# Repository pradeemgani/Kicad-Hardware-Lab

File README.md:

# 🔧 KiCad Hardware Lab

A collection of practical electronics and PCB design projects developed using **KiCad**.

This repository documents my hands-on work in **analog electronics, digital electronics, power electronics, PCB design, and embedded hardware**.

---

## 📚 Projects

| # | Project | Category |
|---|---|---|
| 1 | BJT AMPLIFIER | Analog  Electronics |
| 2 | Full Wave Rectifier | Power Electronics |
| 3 | Half Wave Rectifier | Power Electronics |
| 4 | Inverting Amplifier | Analog Electronics |
| 5 | JK FLIP FLOP | Digital Electronics |
| 6 | RC PHASE SHIFT OSCILLATOR | Analog Electronics |
| 7 | SIMPLE CONTINUITY TESTER | Analog/Discrete Electronics |
| 8 | Regulator POWER SUPPLY | Power Electronics |

More projects will be added as the hardware design work continues.

---

## 🛠️ Tools & Technologies

- **KiCad** – Schematic capture and PCB design
- **PCB Layout & Design**
- **Electronic Circuit Design**
- **Analog Electronics**
- **Digital Electronics**
- **Power Electronics**
- **Gerber Generation**
- **PCB Fabrication Preparation**

---

## 📂 Repository Structure

Each project contains the KiCad design files required to open and continue working on the project.

```text
KiCad-Hardware-Lab/
│
├── /BJT AMPLIFIER
├── Full-Wave-Rectifier/
├── Half-Wave-Rectifier/
├── Inverting-Amplifier/
├── JK FLIP FLOP/
├── RC PHASE SHIFT OSCILLATOR/
├── SIMPLE CONTINUITY TESTER/
├── Regulator POWER SUPPLY/
│
└── README.md

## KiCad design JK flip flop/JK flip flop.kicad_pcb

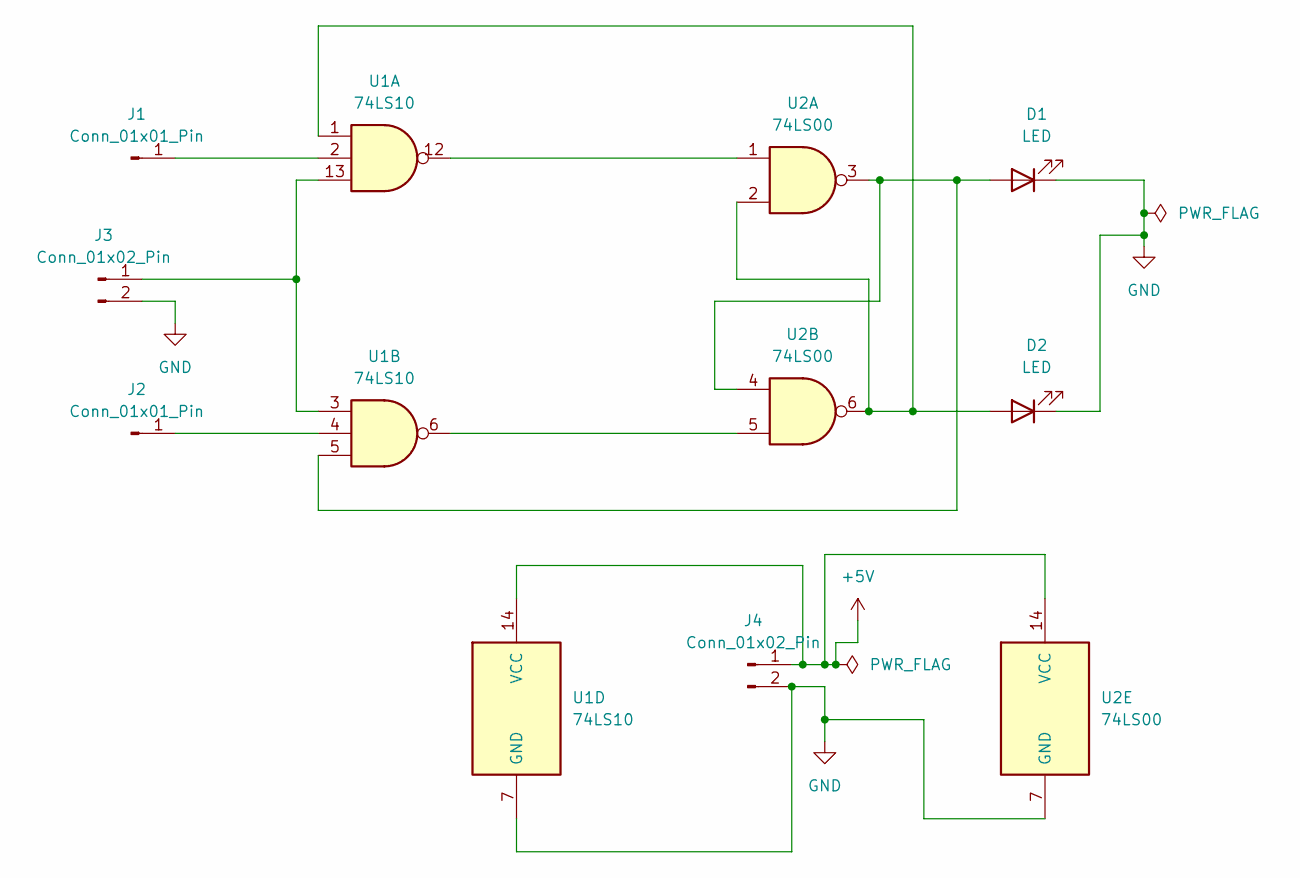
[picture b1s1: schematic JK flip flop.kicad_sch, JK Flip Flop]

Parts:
D1, D2: LED; LED_D5.0mm
J1, J2: Conn_01x01_Pin; PinHeader_1x01_P2.54mm_Vertical
J3, J4: Conn_01x02_Pin; PinHeader_1x02_P2.54mm_Vertical
U1: 74LS10; DIP-14_W7.62mm
U2: 74LS00; DIP-14_W7.62mm

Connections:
+5V: J4.1, U1.14 (VCC), U2.14 (VCC)
GND: D1.1 (K), D2.1 (K), J3.2, J4.2, U1.7 (GND), U2.7 (GND)
unnamed: D1.2 (A), U1.5, U2.3, U2.4
unnamed: D2.2 (A), U1.1, U2.2, U2.6
unnamed: J1.1 (Pin_1_1), U1.2
unnamed: J2.1 (Pin_1_1), U1.4
unnamed: J3.1, U1.3, U1.13
unnamed: U1.6, U2.5
unnamed: U1.12, U2.1

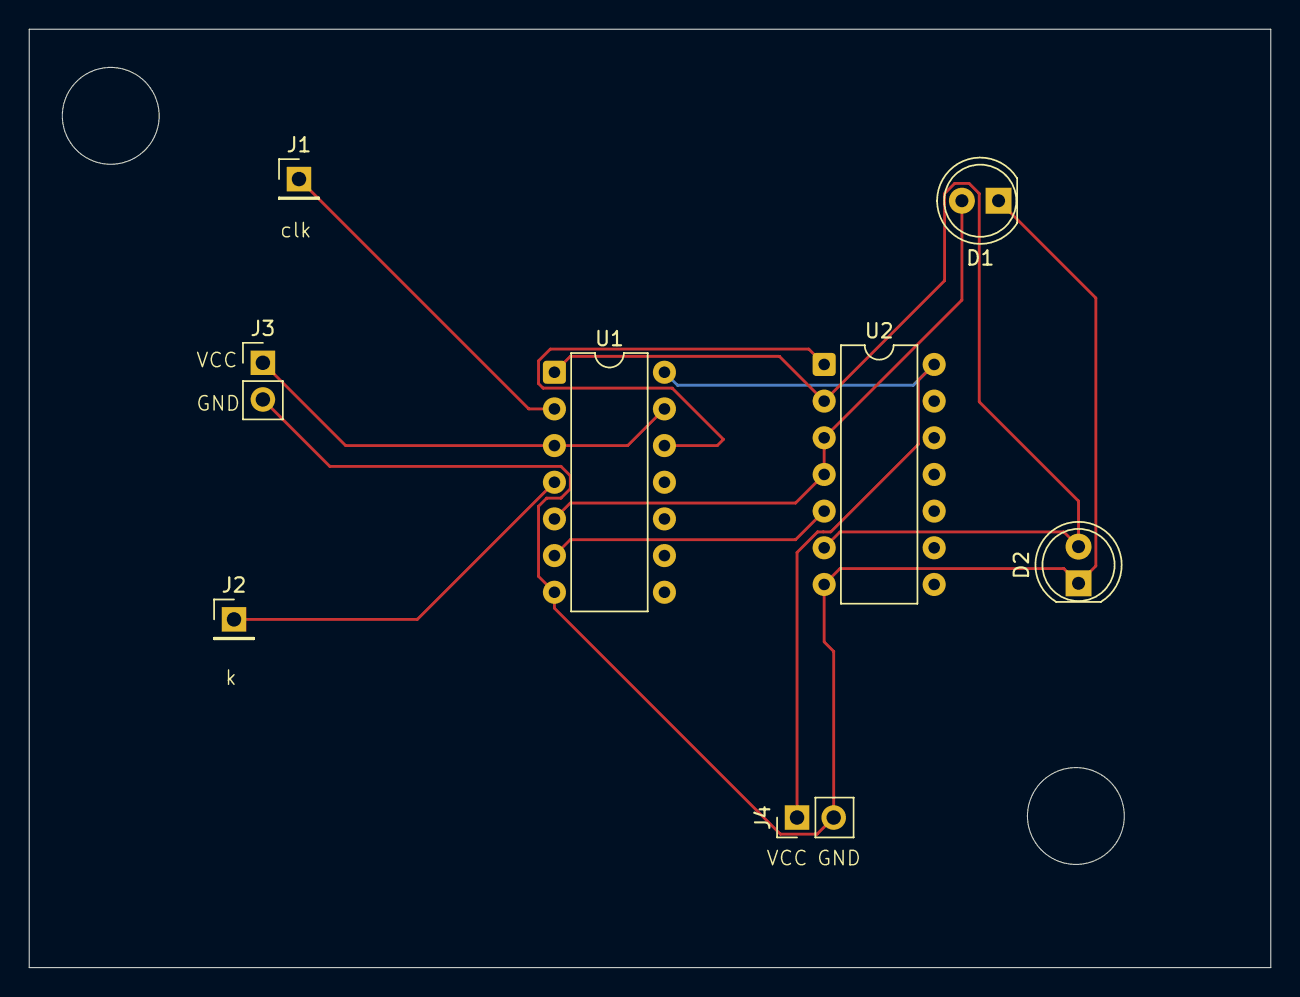
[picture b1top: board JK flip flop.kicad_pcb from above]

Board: 2 copper layers, 86.0 x 65.0 mm, 8 parts (0 on the bottom side), 9 nets.

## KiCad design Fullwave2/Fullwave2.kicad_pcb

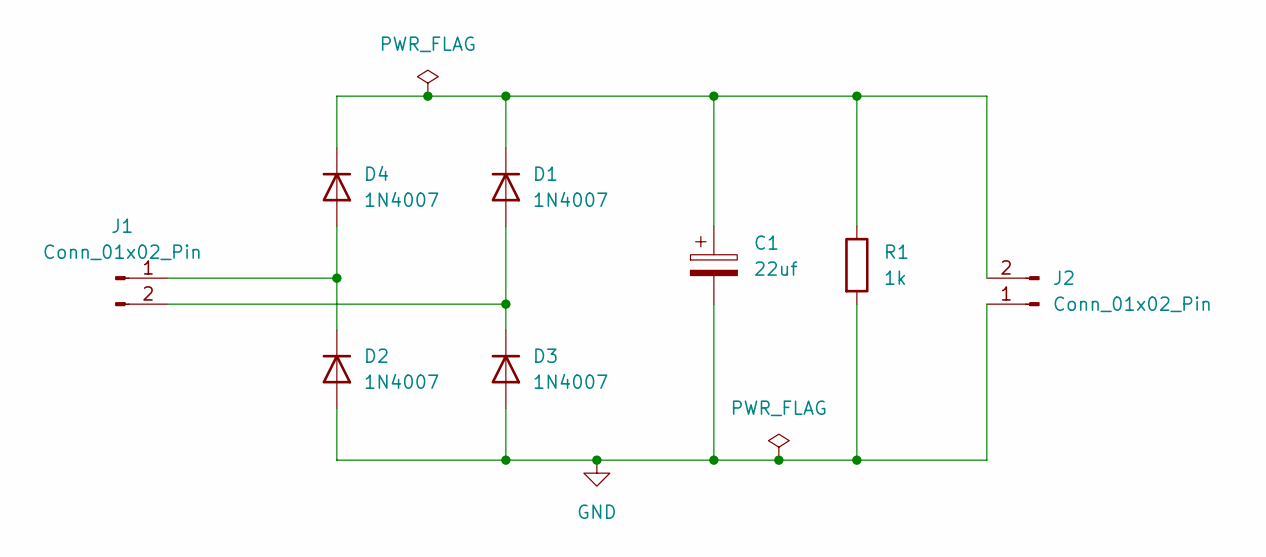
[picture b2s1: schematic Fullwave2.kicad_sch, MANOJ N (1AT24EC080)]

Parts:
C1: 22uf; CP_Radial_D6.3mm_P2.50mm
D1, D2, D3, D4: 1N4007; D_DO-41_SOD81_P10.16mm_Horizontal
J1, J2: Conn_01x02_Pin; PinHeader_1x02_P2.54mm_Vertical
R1: 1k; R_Axial_DIN0207_L6.3mm_D2.5mm_P10.16mm_Horizontal

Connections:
GND: C1.2, D2.2 (A), D3.2 (A), J2.1, R1.2
unnamed: D1.2 (A), D3.1 (K), J1.2
unnamed: C1.1, D1.1 (K), D4.1 (K), J2.2, R1.1
unnamed: D2.1 (K), D4.2 (A), J1.1

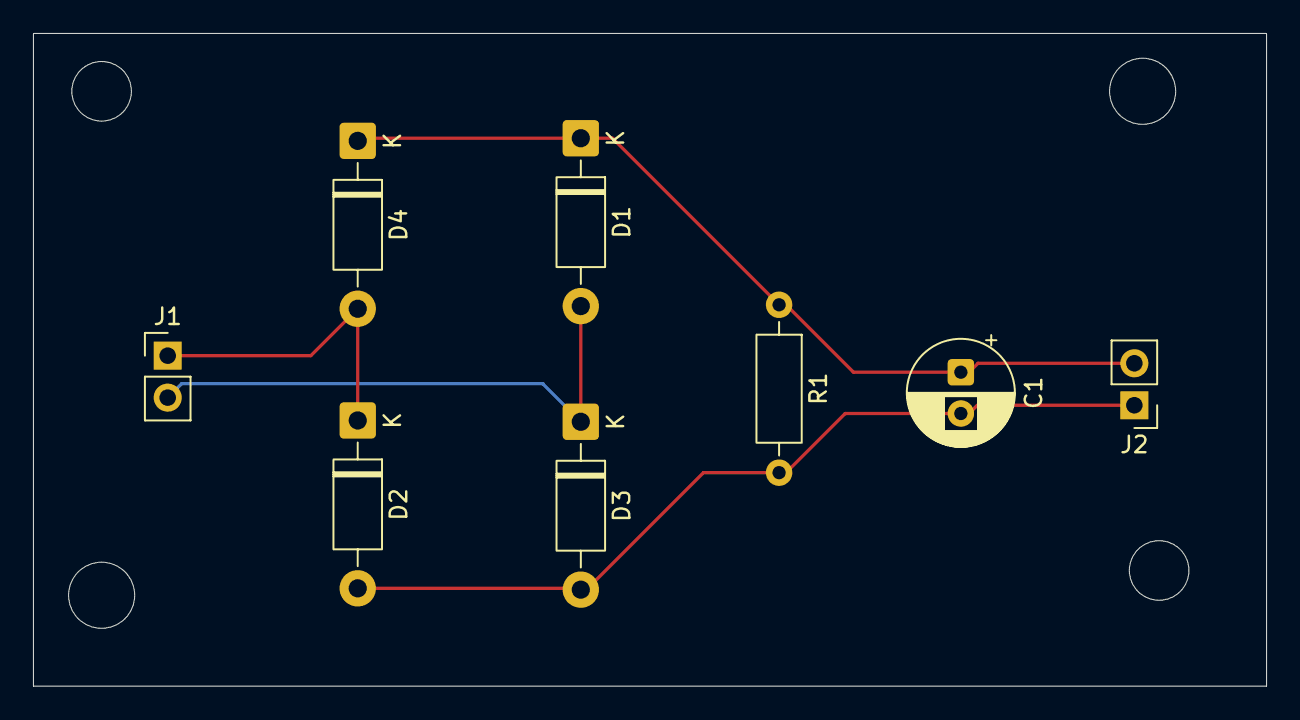
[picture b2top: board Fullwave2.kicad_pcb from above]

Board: 2 copper layers, 74.6 x 39.5 mm, 8 parts (0 on the bottom side), 4 nets.

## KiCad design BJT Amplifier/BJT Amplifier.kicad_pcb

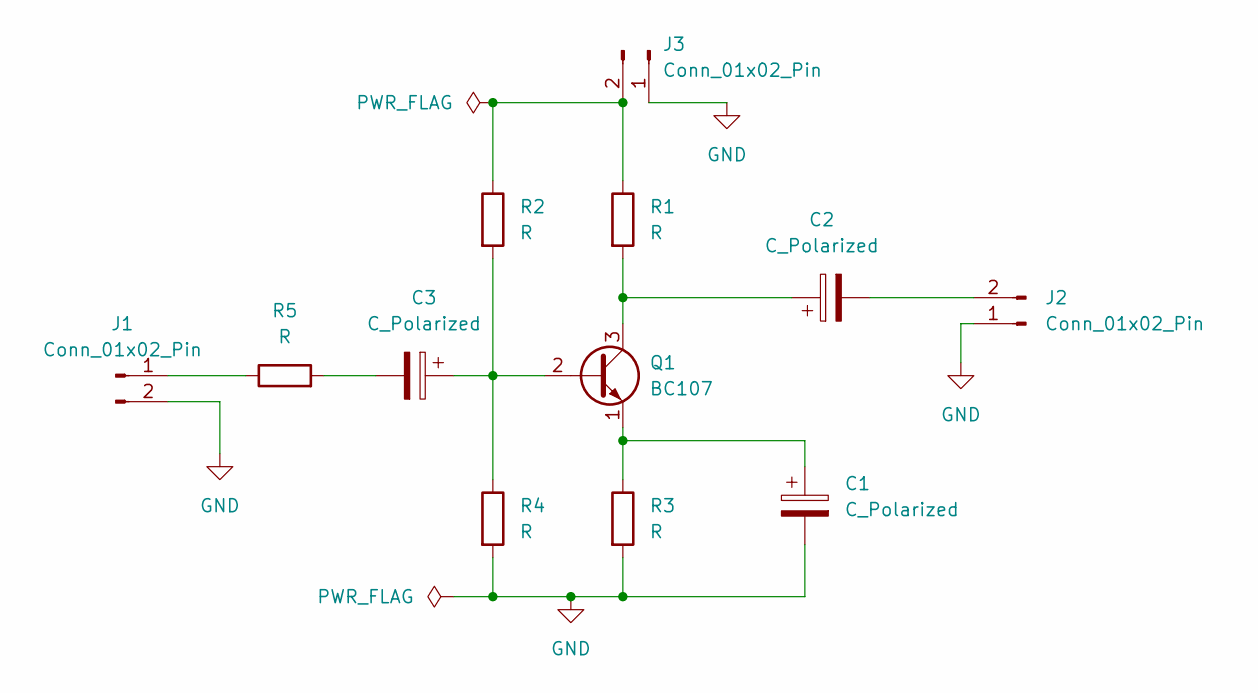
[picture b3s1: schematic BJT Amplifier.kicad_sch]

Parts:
C1, C2, C3: C_Polarized; CP_Radial_D5.0mm_P2.50mm
J1, J2, J3: Conn_01x02_Pin; PinHeader_1x02_P2.54mm_Vertical
Q1: BC107; TO-18-3
R1, R2, R3, R4, R5: R; R_Axial_DIN0207_L6.3mm_D2.5mm_P10.16mm_Horizontal

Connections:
GND: C1.2, J1.2, J2.1, J3.1, R3.2, R4.2
unnamed: C3.2, R5.2
unnamed: J1.1, R5.1
unnamed: C2.2, J2.2
unnamed: J3.2, R1.1, R2.1
unnamed: C3.1, Q1.2 (B), R2.2, R4.1
unnamed: C2.1, Q1.3 (C), R1.2
unnamed: C1.1, Q1.1 (E), R3.1

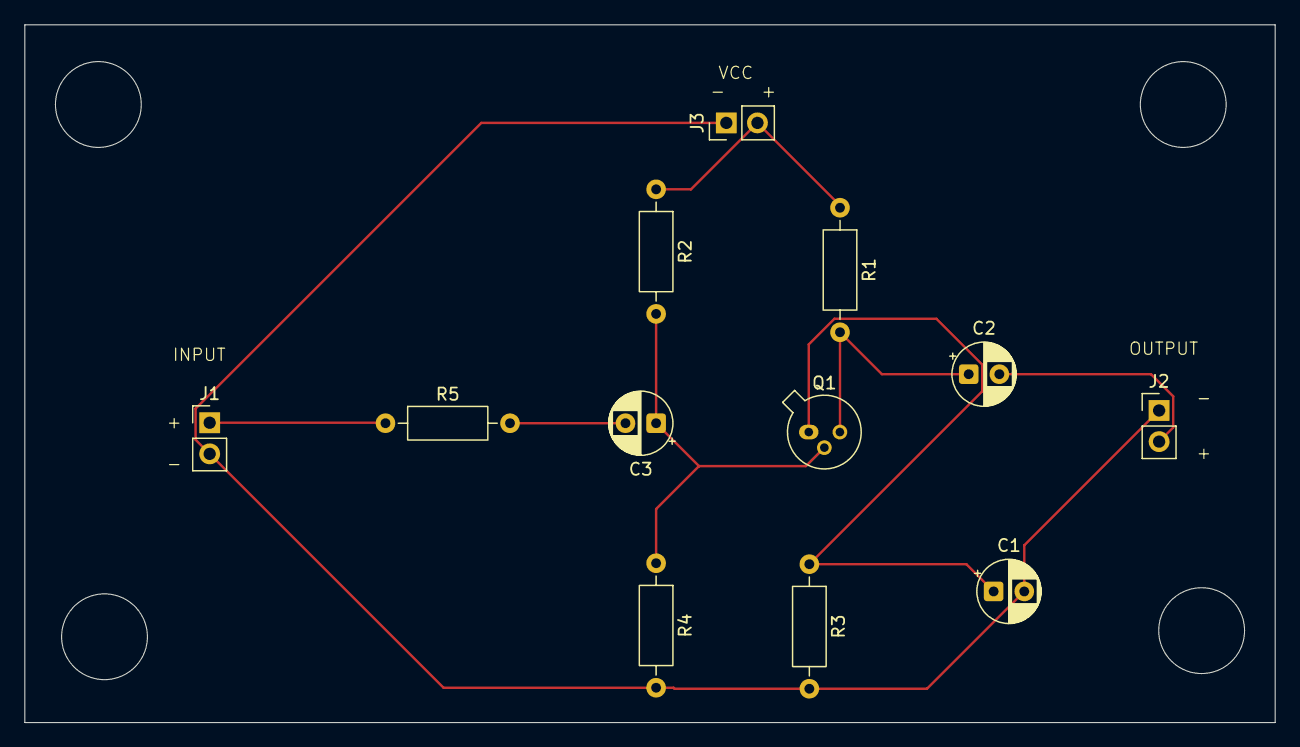
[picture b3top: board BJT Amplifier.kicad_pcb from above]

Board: 2 copper layers, 102.0 x 56.9 mm, 12 parts (0 on the bottom side), 8 nets.

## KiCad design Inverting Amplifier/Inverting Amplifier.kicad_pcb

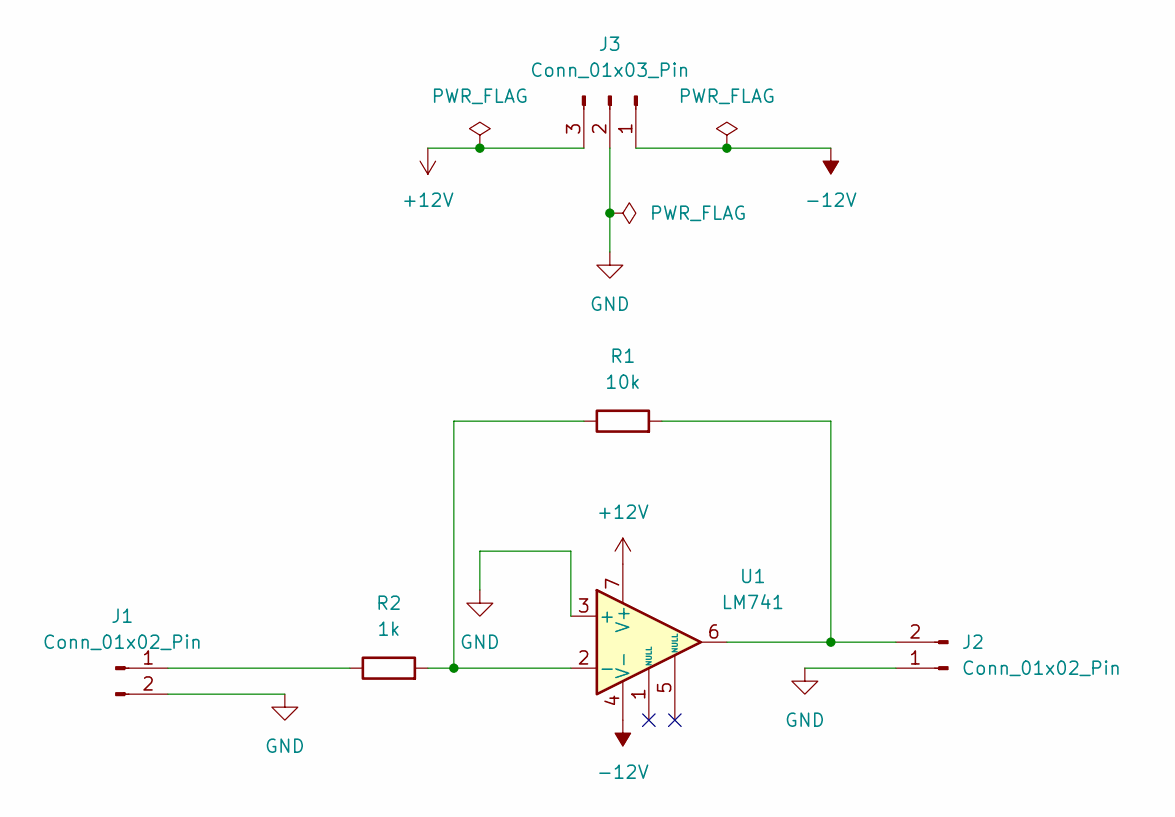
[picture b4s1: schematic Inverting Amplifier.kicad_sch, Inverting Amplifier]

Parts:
J1, J2: Conn_01x02_Pin; PinHeader_1x02_P2.54mm_Vertical
J3: Conn_01x03_Pin; PinSocket_1x03_P2.54mm_Vertical
R1: 10k; R_Axial_DIN0207_L6.3mm_D2.5mm_P10.16mm_Horizontal
R2: 1k; R_Axial_DIN0207_L6.3mm_D2.5mm_P10.16mm_Horizontal
U1: LM741; DIP-8_W7.62mm_LongPads

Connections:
+12V: J3.3, U1.7 (V+)
-12V: J3.1, U1.4 (V-)
GND: J1.2, J2.1, J3.2, U1.3 (+)
unnamed: J1.1, R2.1
unnamed: J2.2, R1.2, U1.6
unnamed: R1.1, R2.2, U1.2 (-)

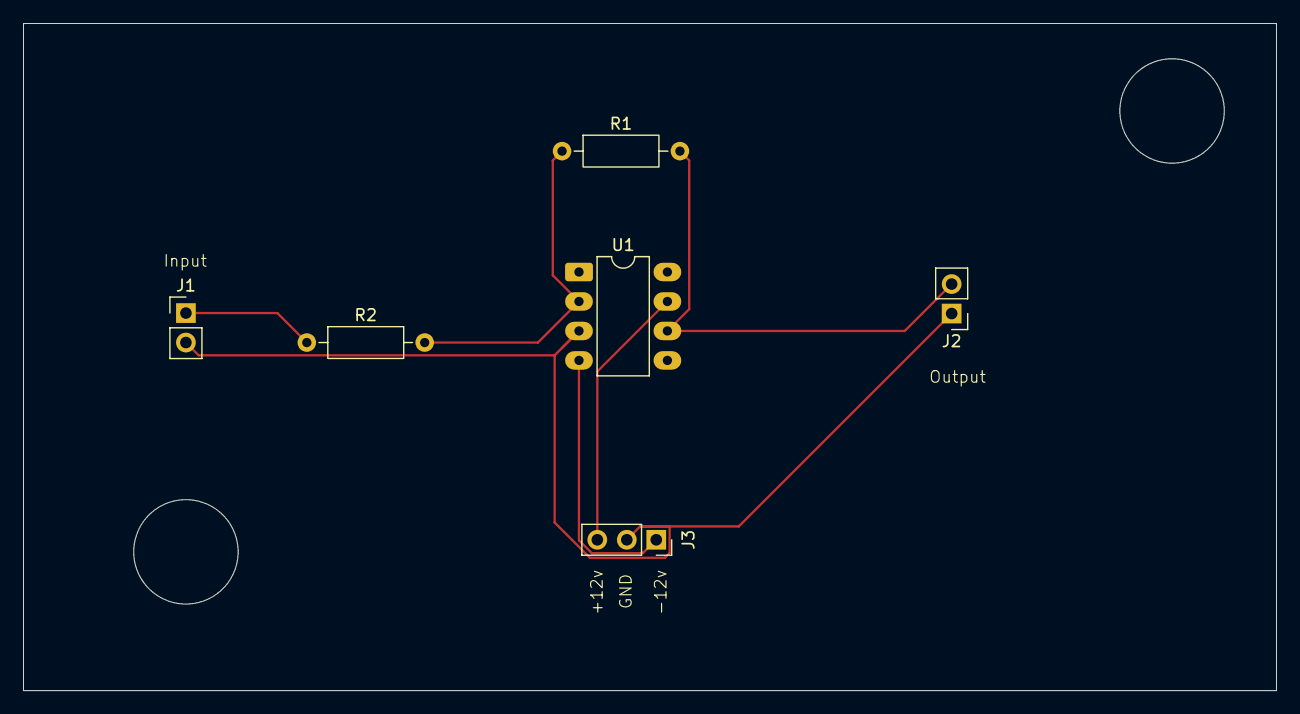
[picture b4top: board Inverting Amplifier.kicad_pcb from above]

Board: 2 copper layers, 108.0 x 57.5 mm, 6 parts (0 on the bottom side), 6 nets.

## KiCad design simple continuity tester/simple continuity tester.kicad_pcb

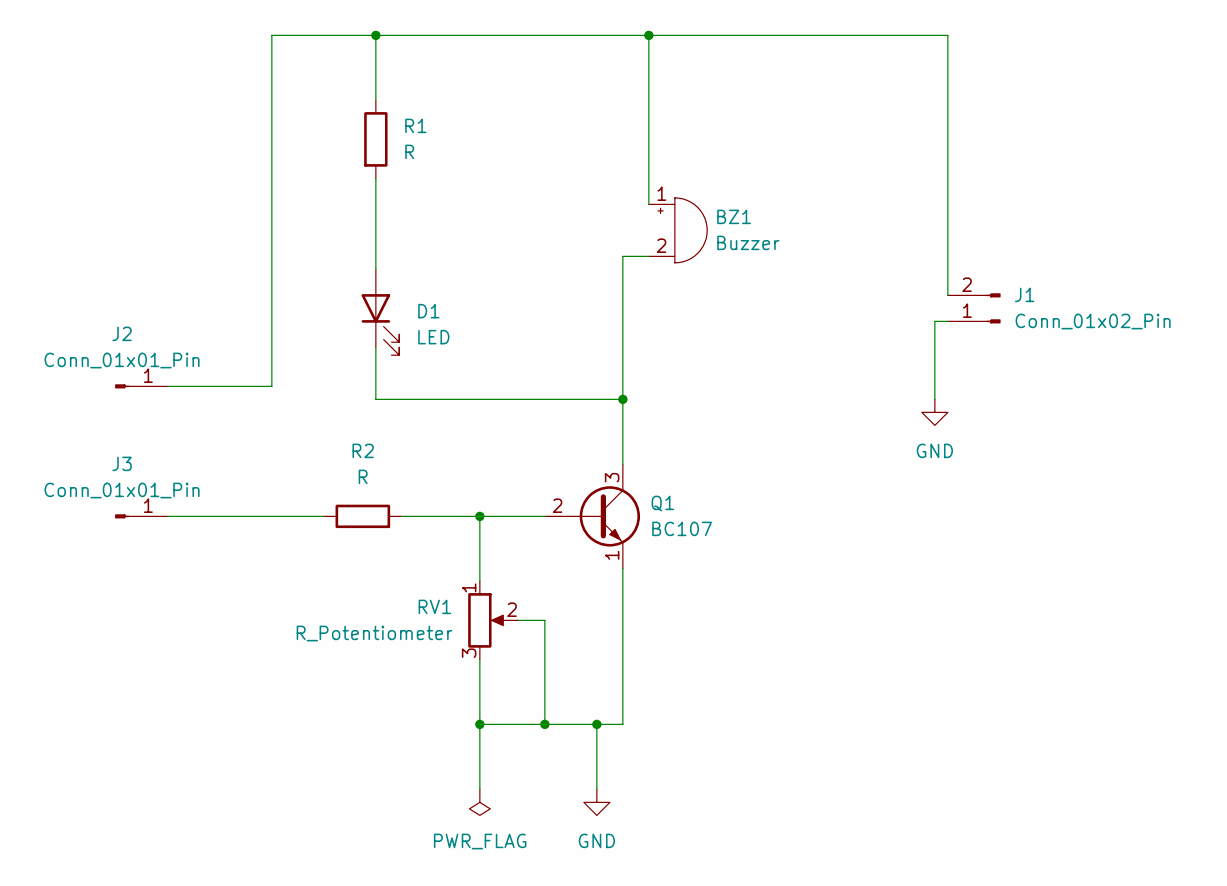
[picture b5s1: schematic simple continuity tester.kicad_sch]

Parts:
BZ1: Buzzer; Buzzer_12x9.5RM7.6
D1: LED; LED_D3.0mm
J1: Conn_01x02_Pin; PinHeader_1x02_P2.54mm_Vertical
J2, J3: Conn_01x01_Pin; PinHeader_1x01_P2.54mm_Vertical
Q1: BC107; TO-18-3
R1, R2: R; R_Axial_DIN0207_L6.3mm_D2.5mm_P10.16mm_Horizontal
RV1: R_Potentiometer; Potentiometer_Bourns_3296W_Vertical

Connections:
GND: J1.1, Q1.1 (E), RV1.2, RV1.3
unnamed: BZ1.1 (+), J1.2, J2.1 (Pin_1_1), R1.1
unnamed: BZ1.2 (-), D1.1 (K), Q1.3 (C)
unnamed: D1.2 (A), R1.2
unnamed: J3.1 (Pin_1_1), R2.1
unnamed: Q1.2 (B), R2.2, RV1.1

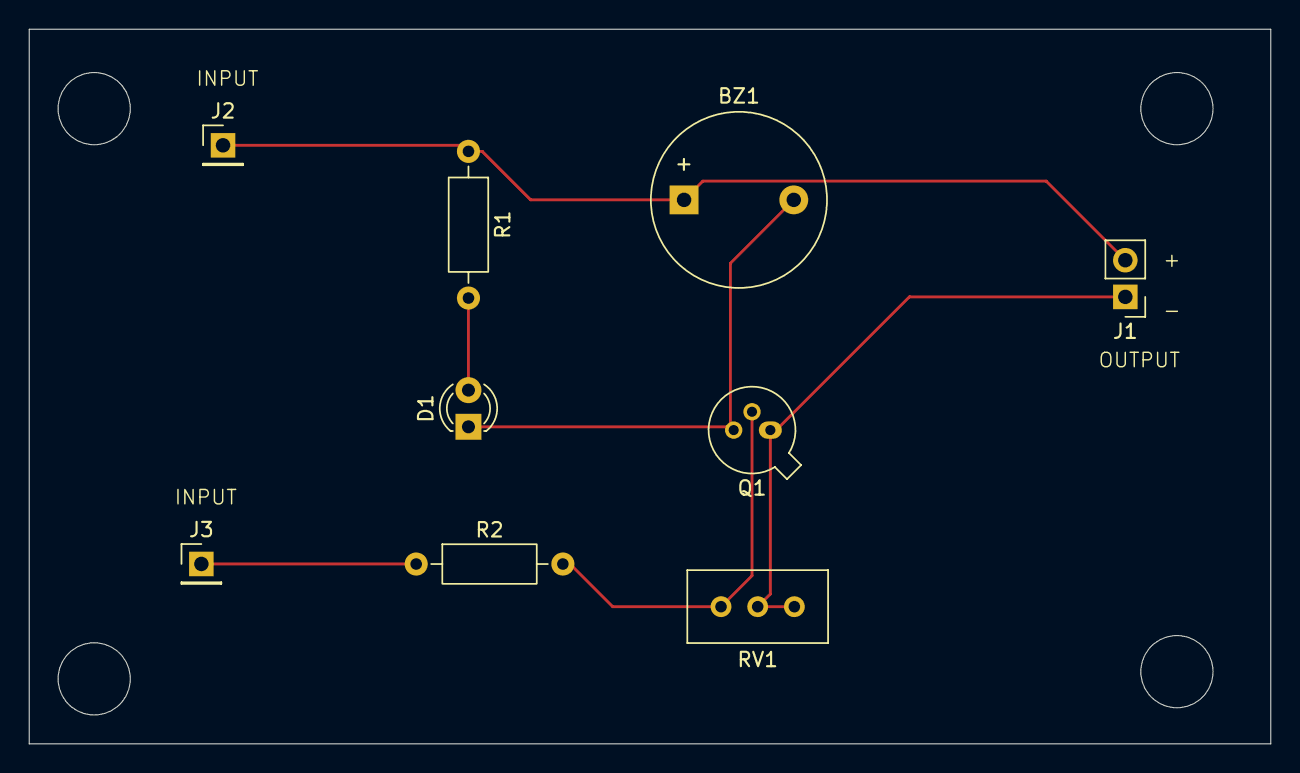
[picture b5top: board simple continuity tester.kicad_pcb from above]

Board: 2 copper layers, 86.0 x 49.5 mm, 9 parts (0 on the bottom side), 6 nets.

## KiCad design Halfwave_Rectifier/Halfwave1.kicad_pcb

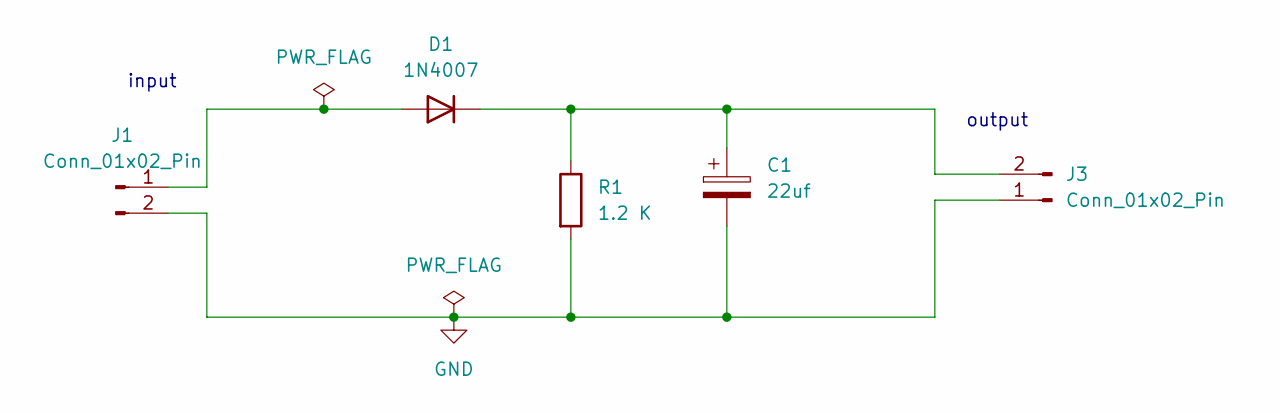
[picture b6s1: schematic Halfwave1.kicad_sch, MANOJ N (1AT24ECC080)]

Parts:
C1: 22uf; CP_Radial_D5.0mm_P2.50mm
D1: 1N4007; D_DO-41_SOD81_P10.16mm_Horizontal
J1, J3: Conn_01x02_Pin; PinHeader_1x02_P2.54mm_Vertical
R1: 1.2 K; R_Axial_DIN0207_L6.3mm_D2.5mm_P10.16mm_Horizontal

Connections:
GND: C1.2, J1.2, J3.1, R1.2
unnamed: D1.2 (A), J1.1
unnamed: C1.1, D1.1 (K), J3.2, R1.1

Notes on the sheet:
input
output

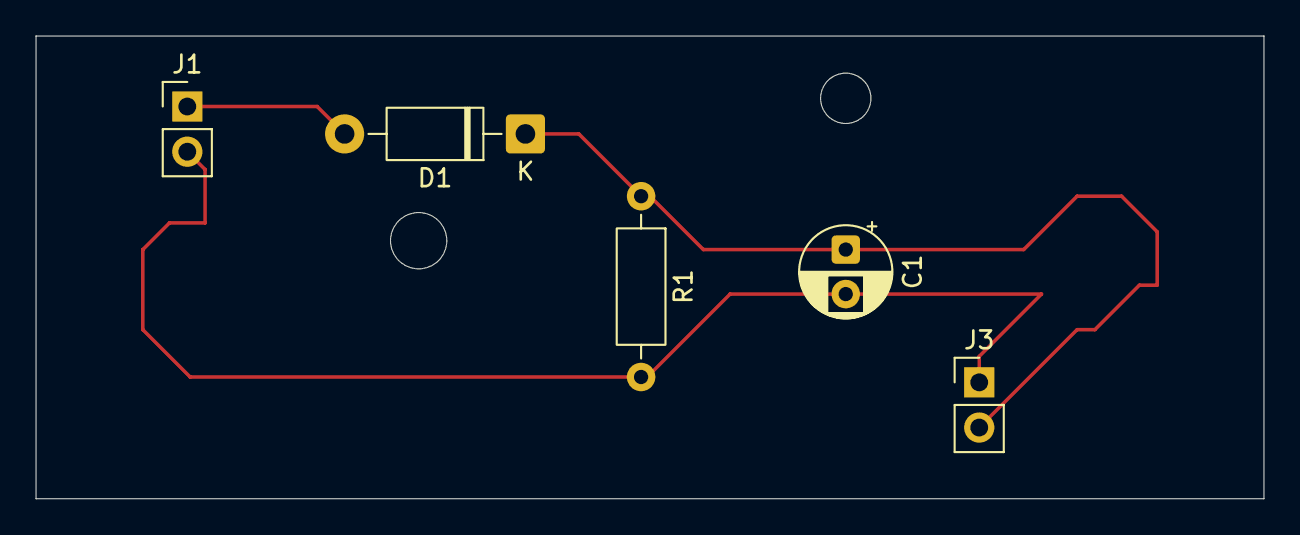
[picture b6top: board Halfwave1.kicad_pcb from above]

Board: 2 copper layers, 69.0 x 26.0 mm, 5 parts (0 on the bottom side), 3 nets.

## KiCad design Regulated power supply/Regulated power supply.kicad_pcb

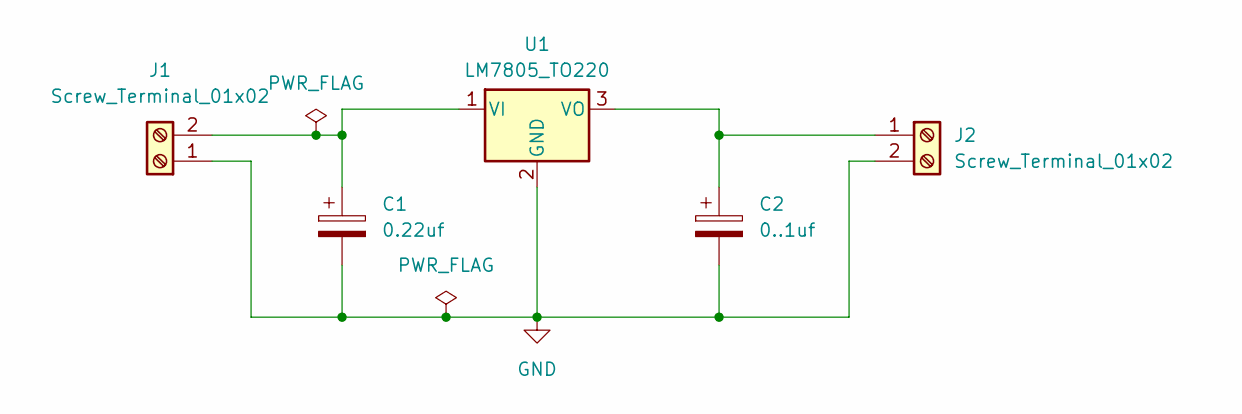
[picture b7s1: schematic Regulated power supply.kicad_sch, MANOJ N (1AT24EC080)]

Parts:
C1: 0.22uf; CP_Radial_D5.0mm_P2.50mm
C2: 0..1uf; CP_Radial_D5.0mm_P2.50mm
J1, J2: Screw_Terminal_01x02; TerminalBlock_Phoenix_PT-1,5-2-3.5-H_1x02_P3.50mm_Horizontal
U1: LM7805_TO220; TO-220-3_Vertical

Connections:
GND: C1.2, C2.2, J1.1, J2.2, U1.2 (GND)
unnamed: C1.1, J1.2, U1.1 (VI)
unnamed: C2.1, J2.1, U1.3 (VO)

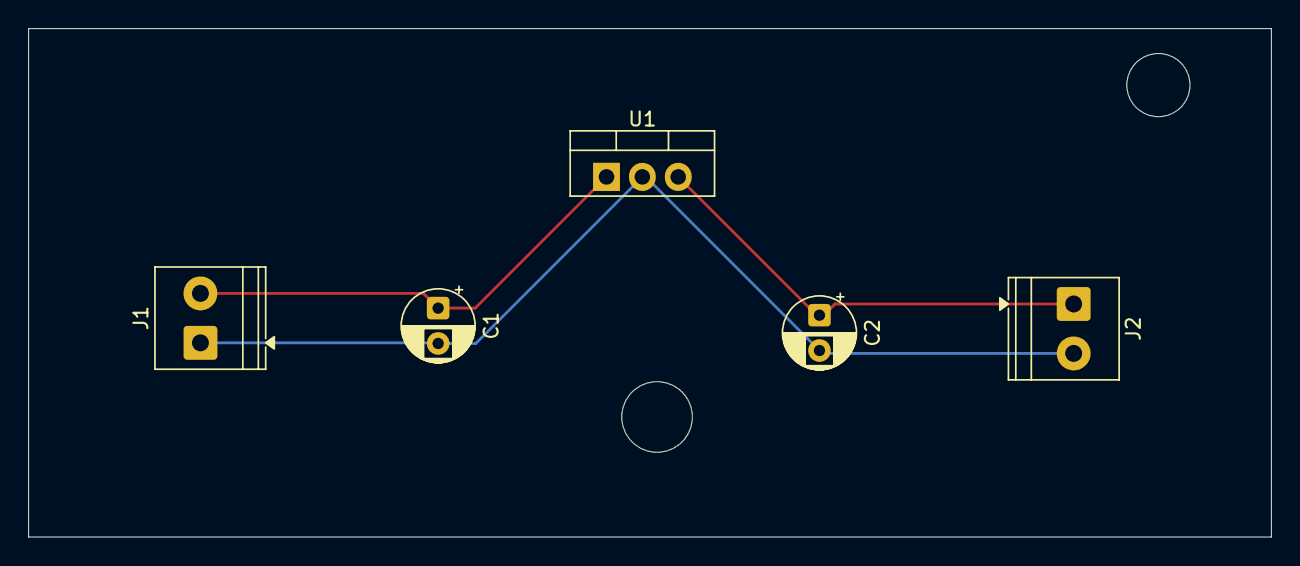
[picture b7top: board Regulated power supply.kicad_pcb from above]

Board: 2 copper layers, 88.0 x 36.0 mm, 5 parts (0 on the bottom side), 3 nets.

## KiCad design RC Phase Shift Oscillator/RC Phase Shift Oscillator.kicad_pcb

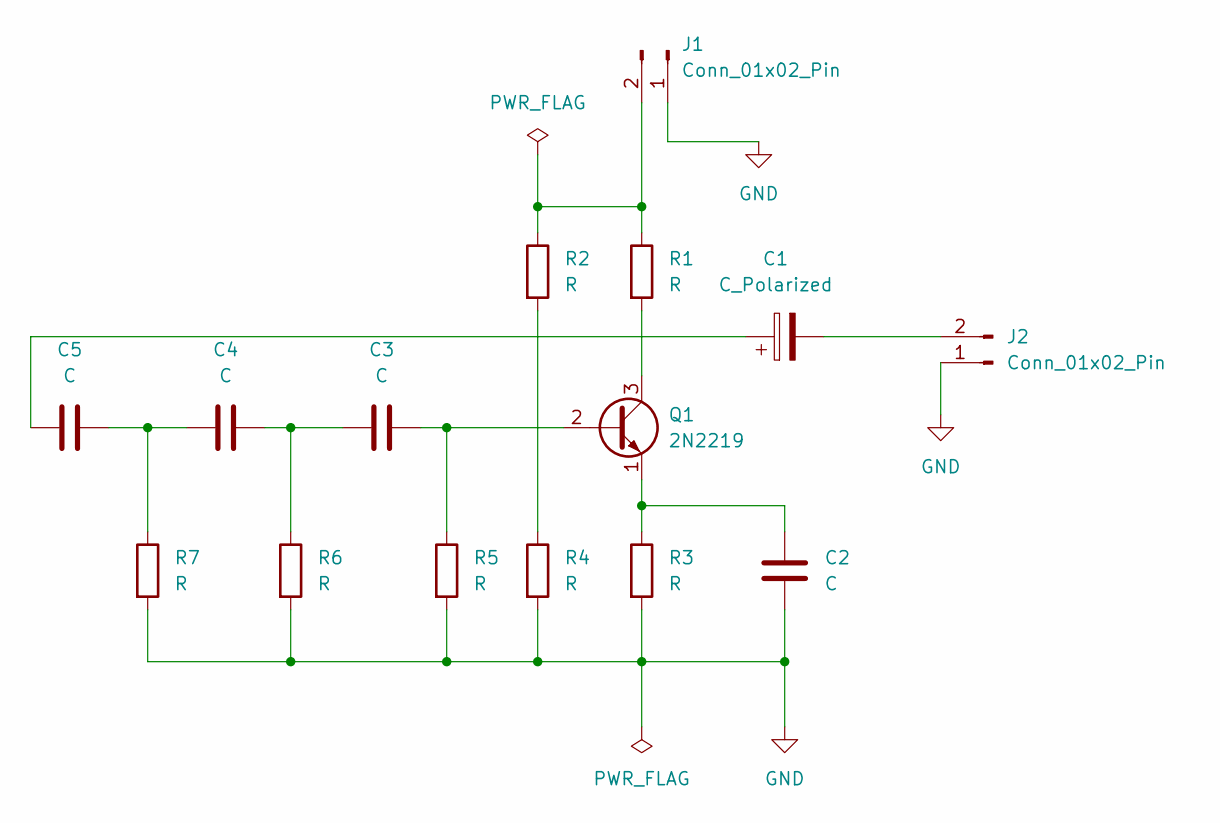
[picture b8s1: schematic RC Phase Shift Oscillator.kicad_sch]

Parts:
C1: C_Polarized; CP_Radial_D5.0mm_P2.50mm
C2, C3, C4, C5: C; C_Disc_D5.0mm_W2.5mm_P2.50mm
J1, J2: Conn_01x02_Pin; PinHeader_1x02_P2.54mm_Vertical
Q1: 2N2219; TO-39-3
R1, R2, R3, R4, R5, R6, R7: R; R_Axial_DIN0207_L6.3mm_D2.5mm_P10.16mm_Horizontal

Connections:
GND: C2.2, J1.1, J2.1, R3.2, R4.2, R5.2, R6.2, R7.2
unnamed: C1.1, C5.1
unnamed: C3.1, C4.2, R6.1
unnamed: C4.1, C5.2, R7.1
unnamed: J1.2, R1.1, R2.1
unnamed: C1.2, J2.2
unnamed: C3.2, Q1.2 (B), R5.1
unnamed: Q1.3 (C), R1.2
unnamed: C2.1, Q1.1 (E), R3.1
unnamed: R2.2, R4.1

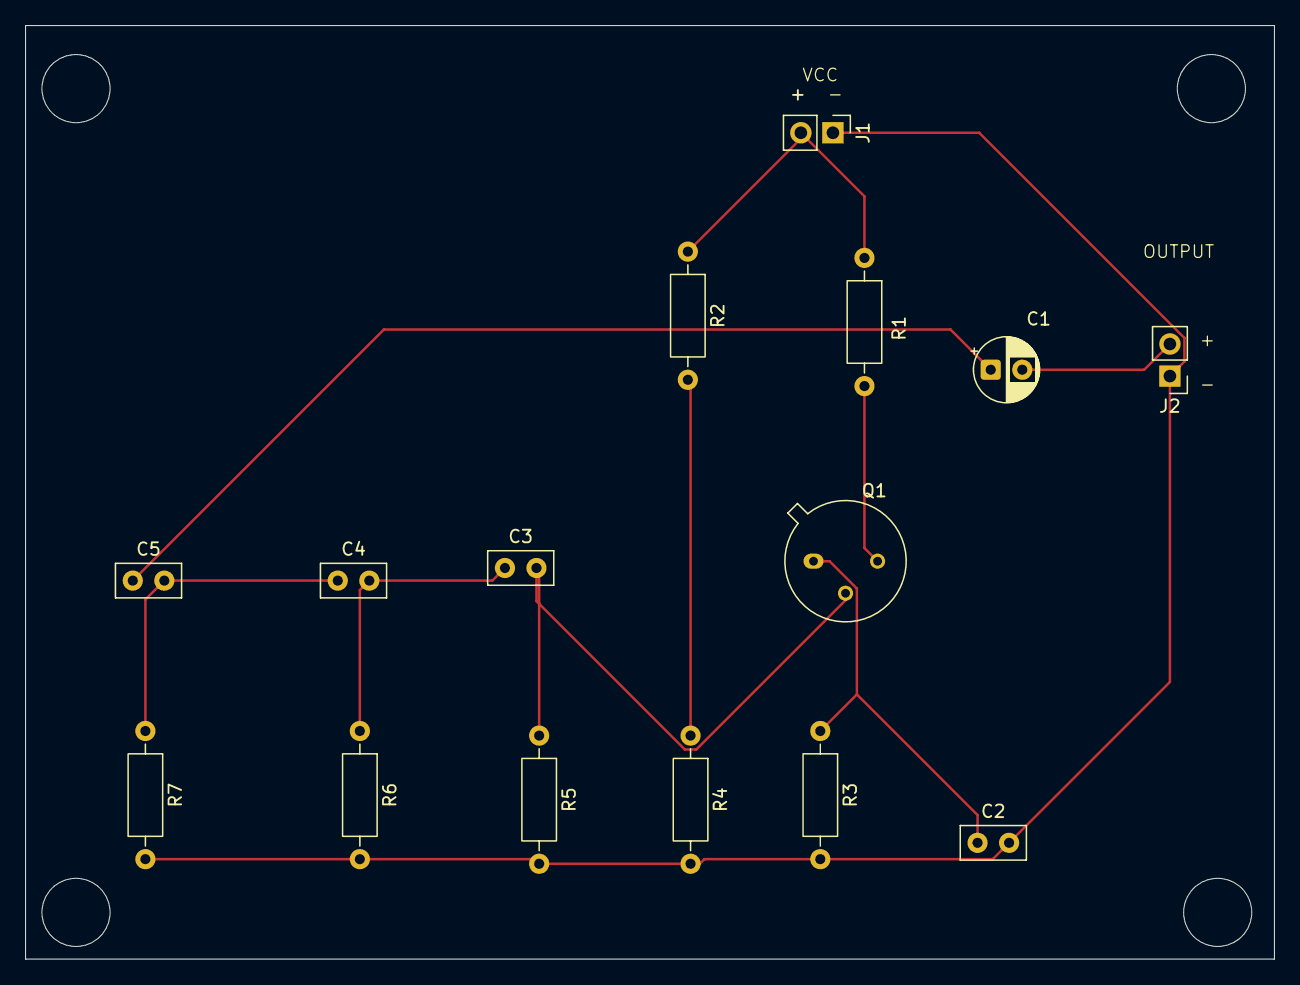
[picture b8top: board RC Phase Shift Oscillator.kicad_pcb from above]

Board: 2 copper layers, 99.0 x 74.0 mm, 15 parts (0 on the bottom side), 10 nets.
